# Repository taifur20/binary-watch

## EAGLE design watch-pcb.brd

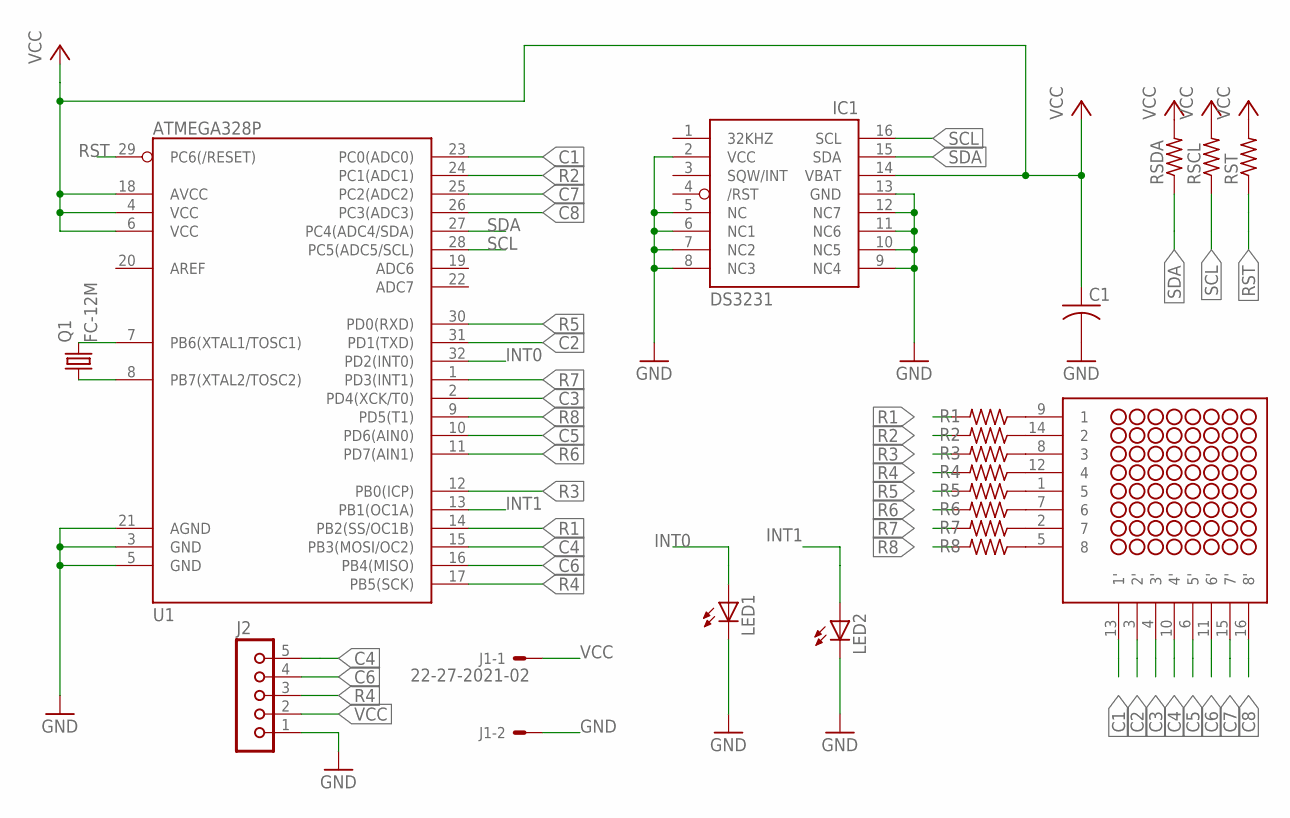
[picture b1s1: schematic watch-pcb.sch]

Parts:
C1: C-USC0805K; C0805K
IC1: DS3231/SO; SO16W
J1: 22-27-2021-02; 6410-02
J2: JU05
LED1, LED2: LED5MM
Q1: FC-12M
R1, R2, R3, R4, R5, R6, R7, R8: R-US_M1406; M1406
RSCL: R-US_M1406; M1406
RSDA: R-US_M1406; M1406
RST: R-US_M1406; M1406
U1: ATMEGA328P; TQFP32-08
U$1: NFM-12881BG-11

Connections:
C1: U1.23 (PC0(ADC0)), U$1.13 (1')
C2: U1.31 (PD1(TXD)), U$1.3 (2')
C3: U1.2 (PD4(XCK/T0)), U$1.4 (3')
C4: J2.5, U1.15 (PB3(MOSI/OC2)), U$1.10 (4')
C5: U1.10 (PD6(AIN0)), U$1.6 (5')
C6: J2.4, U1.16 (PB4(MISO)), U$1.11 (6')
C7: U1.25 (PC2(ADC2)), U$1.15 (7')
C8: U1.26 (PC3(ADC3)), U$1.16 (8')
GND: C1.2, IC1.2 (VCC), IC1.5 (NC), IC1.6 (NC1), IC1.7 (NC2), IC1.8 (NC3), IC1.9 (NC4), IC1.10 (NC5), IC1.11 (NC6), IC1.12 (NC7), IC1.13 (GND), J1.2, J2.1, LED1.K (C), LED2.K (C), U1.3 (GND), U1.5 (GND), U1.21 (AGND)
INT0: LED1.A, U1.32 (PD2(INT0))
INT1: LED2.A, U1.13 (PB1(OC1A))
unnamed: R1.1, U$1.9 (1)
unnamed: R2.1, U$1.14 (2)
unnamed: R3.1, U$1.8 (3)
unnamed: R4.1, U$1.12 (4)
unnamed: R5.1, U$1.1 (5)
unnamed: R6.1, U$1.7 (6)
unnamed: R7.1, U$1.2 (7)
unnamed: R8.1, U$1.5 (8)
unnamed: Q1.2, U1.7 (PB6(XTAL1/TOSC1))
unnamed: Q1.1, U1.8 (PB7(XTAL2/TOSC2))
R1: R1.2, U1.14 (PB2(SS/OC1B))
R2: R2.2, U1.24 (PC1(ADC1))
R3: R3.2, U1.12 (PB0(ICP))
R4: J2.3, R4.2, U1.17 (PB5(SCK))
R5: R5.2, U1.30 (PD0(RXD))
R6: R6.2, U1.11 (PD7(AIN1))
R7: R7.2, U1.1 (PD3(INT1))
R8: R8.2, U1.9 (PD5(T1))
RST: RST.1, U1.29 (PC6(/RESET))
SCL: IC1.16 (SCL), RSCL.1, U1.28 (PC5(ADC5/SCL))
SDA: IC1.15 (SDA), RSDA.1, U1.27 (PC4(ADC4/SDA))
VCC: C1.1, IC1.14 (VBAT), J1.1, J2.2, RSCL.2, RSDA.2, RST.2, U1.4 (VCC), U1.6 (VCC), U1.18 (AVCC)

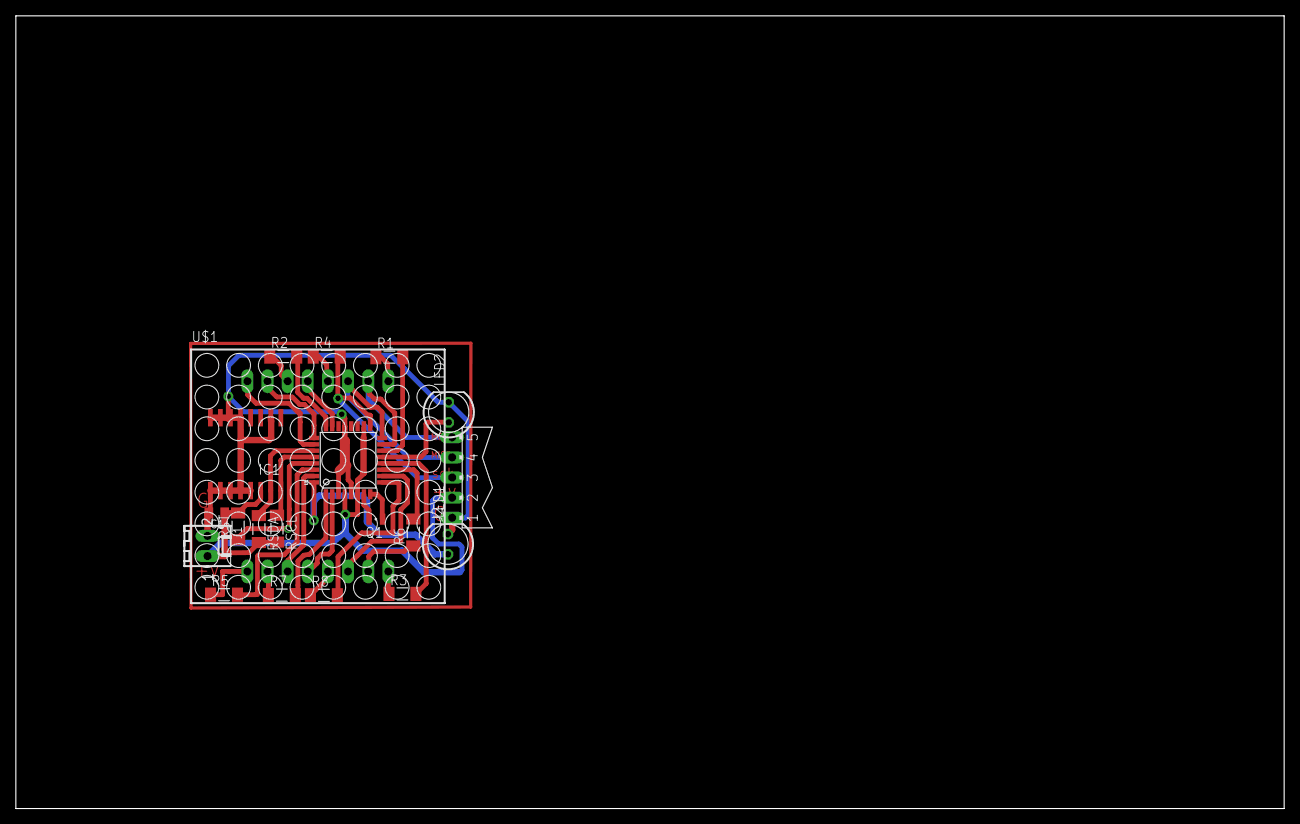
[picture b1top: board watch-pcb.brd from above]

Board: 2 copper layers, 160.0 x 100.0 mm, 20 parts (0 on the bottom side), 33 nets.

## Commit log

2016-01-29 :tada: Added .gitattributes & .gitignore files
2016-01-29 binary-watch
    source code

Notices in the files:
parts and their libraries:
SparkFun-DigitalIC: Licensing: CC v3.0 Share-Alike You are welcome to use this library for commercial purposes.
eagle-library-edeca.net-v5: This is v1 and is licensed under the Creative Commons (Attribution-Non-Commercial-Share Alike 2.0 UK)
